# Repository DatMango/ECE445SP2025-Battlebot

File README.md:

# ECE445SP2025-Battlebot
UIUC ECE 445 Spring 2025 - Senior Design Repository

## Project: Ant-weight, 3D Printed Battlebot
Name of Battlebot: Ant-weight Battlebot - Scooper

## Team Members:
- Justin Leong (jyleong2@illinois.edu)
- Yuxuan Nan (yuxuann2@illinois.edu)
- Zilong Jiang (zjian4@illinois.edu)

## TA:
- Bill Yang (hy38@illinois.edu)

## Problem
The issue at hand is an Ant-weight, 3D Printed Battlebot Competition in which each team wants to win. There are certain constraints of the Battlebots’ design in order to be eligible and win. To win the competition, the goal of a battlebot is to outlast or destroy the opponent team’s battlebot. Different teams will have different designs, meaning a battlebot designed for winning must take into account as many factors to withstand and outlast the competition.

## Solution
We decided upon developing a 3D Printed Bluetooth-controlled battle bot powered by an ESP32 microcontroller. The Battlebot communicates with a PC via a Bluetooth module, enabling wireless command and control. It is equipped with two DC motors driven by H-bridge circuits for precise movement and a ramp-shaped weapon system for engaging in battles. The ESP32 manages motor control using GPIO and PWM, while the weapon system utilizes GPIO. The bot integrates real-time communication, robust motor control, and weapon functionality, offering an engaging and functional design. My goal is to create a responsive and competitive robot for dynamic competitions.

## Lab Notebook
[Can be found here!](Documentation/Notebook.md)

## Video!
[Battlebot Intro Video](https://youtu.be/LQH7uXVlK6E)

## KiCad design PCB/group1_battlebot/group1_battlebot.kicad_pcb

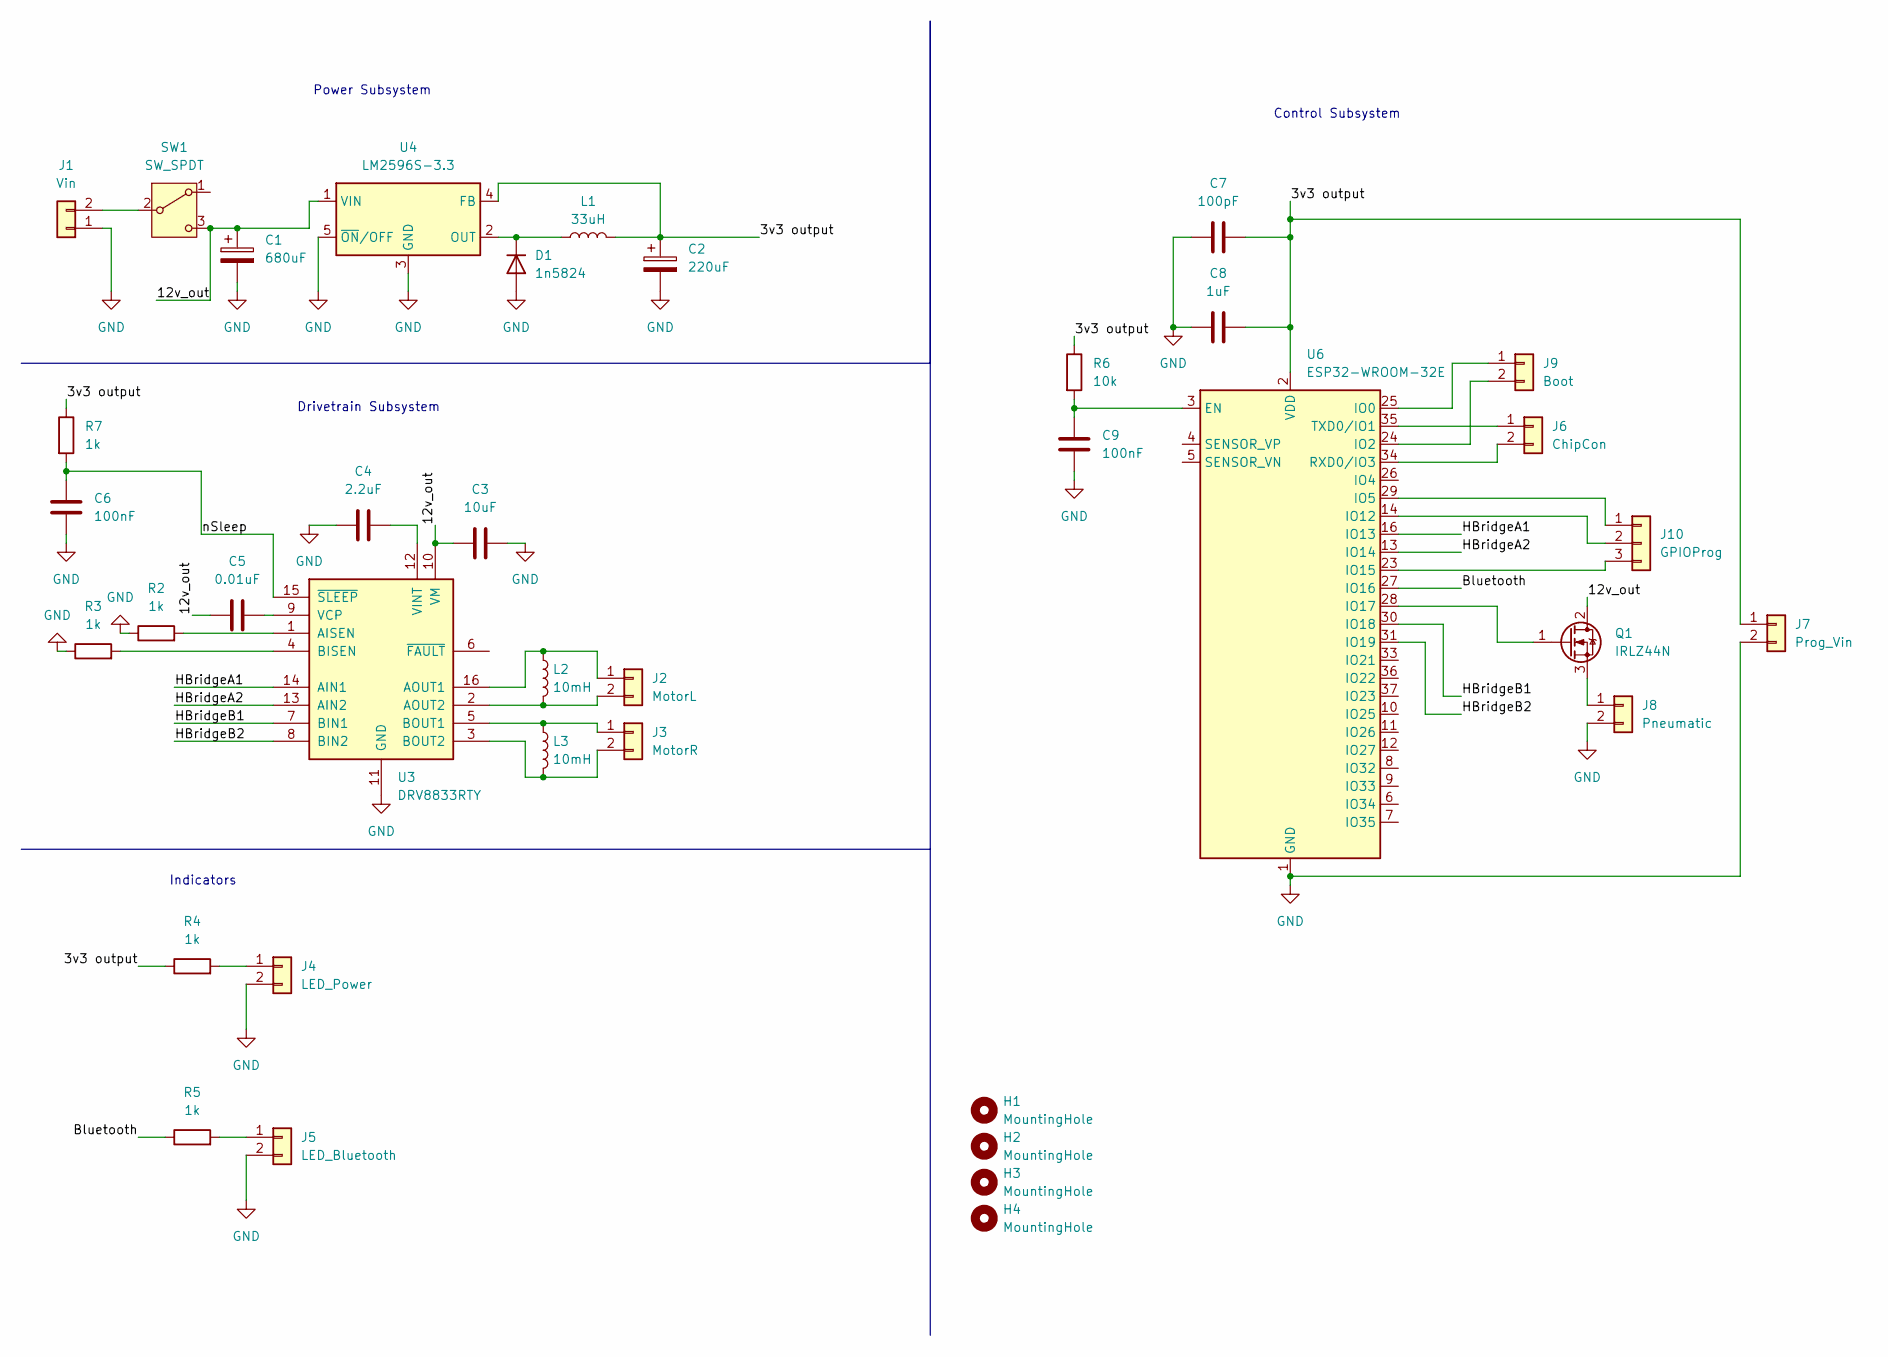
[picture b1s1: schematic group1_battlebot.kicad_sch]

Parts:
C1: 680uF; CP_Radial_D10.0mm_P5.00mm
C2: 220uF; CP_Radial_D12.5mm_P5.00mm
C3: 10uF; C_0805_2012Metric_Pad1.18x1.45mm_HandSolder
C4: 2.2uF; C_0805_2012Metric_Pad1.18x1.45mm_HandSolder
C5: 0.01uF; C_0603_1608Metric_Pad1.08x0.95mm_HandSolder
C6, C9: 100nF; C_0805_2012Metric_Pad1.18x1.45mm_HandSolder
C7: 100pF; C_0805_2012Metric_Pad1.18x1.45mm_HandSolder
C8: 1uF; C_0805_2012Metric_Pad1.18x1.45mm_HandSolder
D1: 1n5824; D_DO-201AD_P3.81mm_Vertical_AnodeUp
H1, H2, H3, H4: MountingHole; MountingHole_3.2mm_M3
J1: Vin; Molex_KK-254_AE-6410-02A_1x02_P2.54mm_Vertical
J2: MotorL; Molex_KK-254_AE-6410-02A_1x02_P2.54mm_Vertical
J3: MotorR; Molex_KK-254_AE-6410-02A_1x02_P2.54mm_Vertical
J4: LED_Power; Molex_KK-254_AE-6410-02A_1x02_P2.54mm_Vertical
J5: LED_Bluetooth; Molex_KK-254_AE-6410-02A_1x02_P2.54mm_Vertical
J6: ChipCon; Molex_KK-254_AE-6410-02A_1x02_P2.54mm_Vertical
J7: Prog_Vin; Molex_KK-254_AE-6410-02A_1x02_P2.54mm_Vertical
J8: Pneumatic; Molex_KK-254_AE-6410-02A_1x02_P2.54mm_Vertical
J9: Boot; Molex_KK-254_AE-6410-02A_1x02_P2.54mm_Vertical
J10: GPIOProg; Molex_KK-254_AE-6410-03A_1x03_P2.54mm_Vertical
L1: 33uH; L_0603_1608Metric_Pad1.05x0.95mm_HandSolder
L2, L3: 10mH; L_0603_1608Metric_Pad1.05x0.95mm_HandSolder
Q1: IRLZ44N; TO-220-3_Vertical
R2, R3, R4, R5, R7: 1k; R_0805_2012Metric_Pad1.20x1.40mm_HandSolder
R6: 10k; R_0805_2012Metric_Pad1.20x1.40mm_HandSolder
SW1: SW_SPDT; SW_XKB_DM1-16UD-1
U3: DRV8833RTY; Texas_RTY_WQFN-16-1EP_4x4mm_P0.65mm_EP2.1x2.1mm_ThermalVias
U4: LM2596S-3.3; TO-263-5_TabPin3
U6: ESP32-WROOM-32E; ESP32-WROOM-32D

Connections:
/3v3 output: C2.1, C7.2, C8.1, J7.1, L1.2, R4.1, R6.1, R7.1, U4.4 (FB), U6.2 (VDD)
/12v_out: C1.1, C3.2, C5.1, Q1.2 (D), SW1.3 (C), U3.10 (VM), U4.1 (VIN)
/Bluetooth: R5.1, U6.27 (IO16)
/HBridgeA1: U3.14 (AIN1), U6.16 (IO13)
/HBridgeA2: U3.13 (AIN2), U6.13 (IO14)
/HBridgeB1: U3.7 (BIN1), U6.30 (IO18)
/HBridgeB2: U3.8 (BIN2), U6.31 (IO19)
/nSleep: C6.2, R7.2, U3.15 (~SLEEP)
GND: C1.2, C2.2, C3.1, C4.1, C6.1, C7.1, C8.2, C9.1, D1.2 (A), J1.1, J4.2, J5.2, J7.2, J8.2, R2.1, R3.1, U3.11 (GND), U3.17 (GND), U4.3 (GND), U4.5 (~ON/OFF), U6.1 (GND), U6.15 (GND), U6.38 (GND), U6.39 (GND)
unnamed: D1.1 (K), L1.1, U4.2 (OUT)
unnamed: J1.2, SW1.2 (B)
unnamed: J2.1, L2.1, U3.16 (AOUT1)
unnamed: J2.2, L2.2, U3.2 (AOUT2)
unnamed: J3.1, L3.1, U3.5 (BOUT1)
unnamed: J3.2, L3.2, U3.3 (BOUT2)
unnamed: J4.1, R4.2
unnamed: J5.1, R5.2
unnamed: J6.1, U6.35 (TXD0/IO1)
unnamed: J6.2, U6.34 (RXD0/IO3)
unnamed: J8.1, Q1.3 (S)
unnamed: J9.1, U6.25 (IO0)
unnamed: J9.2, U6.24 (IO2)
unnamed: J10.1, U6.29 (IO5)
unnamed: J10.2, U6.14 (IO12)
unnamed: J10.3, U6.23 (IO15)
unnamed: Q1.1 (G), U6.28 (IO17)
unnamed: R2.2, U3.1 (AISEN)
unnamed: R3.2, U3.4 (BISEN)
unnamed: C5.2, U3.9 (VCP)
unnamed: C4.2, U3.12 (VINT)
unnamed: C9.2, R6.2, U6.3 (EN)

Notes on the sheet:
Control Subsystem
Indicators
Power Subsystem
Drivetrain Subsystem

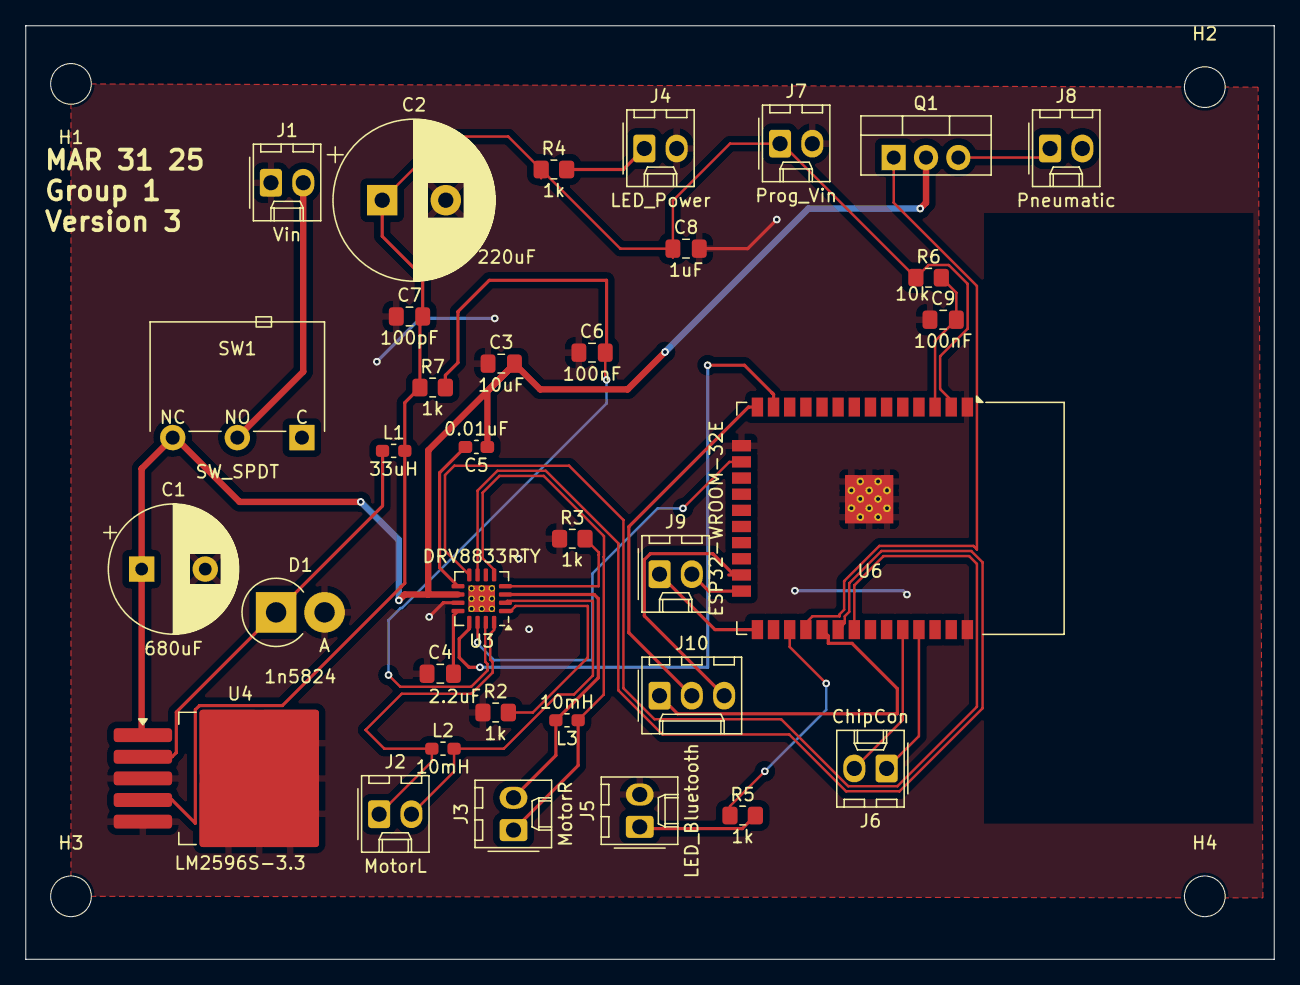
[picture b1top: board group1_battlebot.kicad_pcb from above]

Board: 2 copper layers, 98.2 x 73.4 mm, 38 parts (0 on the bottom side), 31 nets.

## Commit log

2025-05-08 Added Documentation files (i.e. Reports)
2025-05-08 Added team contract as well
2025-05-08 Added some information to lab notebook
2025-05-08 Updated 2/17
2025-05-08 Added Code and PCB
2025-05-08 Added Code and PCB important file locations
2025-05-08 Finished Lab Notebook. Also added all the 3D Print files
2025-05-08 Added YouTube link to the Readme
2025-05-08 Testing Image
2025-05-08 Fixing Images
2025-05-08 Fixed Readme Img
2025-05-08 Fixed Img Centering
2025-05-08 Added Internal Layout Image
2025-05-08 Fixing Internal Layout Image
2025-05-08 Fixed Internal Layout Image
2025-05-08 Added Block Diagram
2025-05-08 PCB Image
2025-05-08 Finished Lab Notebook with more Images
